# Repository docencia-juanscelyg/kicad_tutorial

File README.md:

# Tutorial KiCad

En este breve tutorial se guiará al estudiante en el uso básico del software KiCad. Este software permite diseñar circuitos impresos, es ampliamente usado en la comunidad open source y permite realizar diseños de ingeniería de producto.

<details>
<summary><b>Contenido</b></summary>

- [Instalación](#instalación)
  - [Repositorios de Ubuntu (recomendado)](#repositorios-de-ubuntu-recomendado)
  - [PPA oficial de KiCad](#ppa-oficial-de-kicad)
  - [Flatpak](#flatpak)
  - [Otras plataformas](#otras-plataformas)
  - [Comprobar la instalación](#comprobar-la-instalación)
- [Entorno inicial de trabajo](#entorno-inicial-de-trabajo)
- [Entorno de edición de esquemas](#entorno-de-edición-de-esquemas)
  - [Edición del cajetín](#edición-del-cajetín)
  - [Añadir símbolos](#añadir-símbolos)
  - [Unión entre símbolos](#unión-entre-símbolos)
  - [Añadir símbolos de alimentación](#añadir-símbolos-de-alimentación)
  - [Modificar la huella de un símbolo](#modificar-la-huella-de-un-símbolo)
- [Entorno de edición de placas](#entorno-de-edición-de-placas)
  - [Creación del Edge Cuts](#creación-del-edge-cuts)
  - [Traer o actualizar los cambios desde el esquema](#traer-o-actualizar-los-cambios-desde-el-esquema)
  - [Definir la zona de relleno](#definir-la-zona-de-relleno)
  - [Ubicación de huellas](#ubicación-de-huellas)
  - [Añadir agujeros de montaje](#añadir-agujeros-de-montaje)
  - [Ejecutar el DRC](#ejecutar-el-drc)
  - [Enrutado](#enrutado)
  - [Visualización 3D](#visualización-3d)
  - [Envío a fabricación](#envío-a-fabricación)

</details>

## Instalación

Este tutorial y el proyecto de ejemplo ([ejercicio_1](ejercicio_1/)) se han realizado con **KiCad 7.0** sobre **Ubuntu 24.04**, por lo que se recomienda usar esa misma versión.

> **Importante:** KiCad puede abrir proyectos de versiones anteriores, pero **no** de versiones posteriores. Un proyecto guardado con KiCad 8 o superior ya no se podrá abrir con KiCad 7. Si se trabaja en equipo, todos los miembros deben usar la misma versión.

### Repositorios de Ubuntu (recomendado)

Es la forma más sencilla y la que instala KiCad 7.0 en Ubuntu 24.04. Abrimos una terminal y escribimos:

```bash
sudo apt update
sudo apt install kicad
```

Este comando instala el programa junto con las bibliotecas de símbolos y huellas. La interfaz en español ya viene incluida, por lo que no hace falta instalar ningún paquete de idioma adicional. Opcionalmente se pueden instalar:

- **Modelos 3D de los componentes** (necesarios para la sección de [Visualización 3D](#visualización-3d) y para exportar a `STEP`). Ocupan unos 5,7 GB:

    ```bash
    sudo apt install kicad-packages3d
    ```

- **Ayuda en español** (manuales accesibles desde el menú `Ayuda`):

    ```bash
    sudo apt install kicad-doc-es
    ```

### PPA oficial de KiCad

Si se necesita una versión más reciente, el equipo de KiCad mantiene un repositorio PPA para Ubuntu. Hay un PPA por cada versión principal; en el siguiente ejemplo se usa la 9.0, aunque se puede consultar cuál es la última en la [página de descargas para Ubuntu](https://www.kicad.org/download/ubuntu/):

```bash
sudo add-apt-repository ppa:kicad/kicad-9.0-releases
sudo apt update
sudo apt install kicad
```

> **Nota:** al añadir el PPA, la versión de KiCad 7 instalada desde los repositorios de Ubuntu se sustituirá por la del PPA. Recuerda que los proyectos guardados con esta versión no se podrán abrir en KiCad 7.

### Flatpak

Flatpak permite instalar la última versión de KiCad en cualquier distribución de Linux, de forma aislada del resto del sistema. Si Flatpak no está instalado en Ubuntu, primero hay que instalarlo y añadir el repositorio Flathub (después conviene cerrar sesión y volver a entrar):

```bash
sudo apt install flatpak
flatpak remote-add --if-not-exists flathub https://dl.flathub.org/repo/flathub.flatpakrepo
```

A continuación instalamos KiCad y lo ejecutamos:

```bash
flatpak install flathub org.kicad.KiCad
flatpak run org.kicad.KiCad
```

Los modelos 3D se instalan aparte con `flatpak install flathub org.kicad.KiCad.Library.Packages3D`. Al ejecutarse en un entorno aislado, puede que KiCad no tenga acceso a todas las carpetas del sistema; se recomienda guardar los proyectos dentro de la carpeta personal.

### Otras plataformas

Para Windows, macOS u otras distribuciones de Linux, se puede consultar la [página de descargas de KiCad](https://www.kicad.org/download/).

### Comprobar la instalación

Una vez instalado, KiCad aparecerá en el menú de aplicaciones; también se puede lanzar desde una terminal con el comando `kicad` (o `flatpak run org.kicad.KiCad` si se instaló con Flatpak). La versión instalada se puede consultar en el menú `Ayuda` → `Acerca de KiCad`.

## Entorno inicial de trabajo

Existen dos entornos de trabajo principales: el editor de esquemas y el editor de placas. KiCad incluye otros entornos con los que no trabajaremos en este tutorial. Al abrir el programa aparecerá una ventana principal desde la que podremos gestionar los proyectos que creemos o queramos editar.

Desde esta ventana podremos editar cualquiera de los esquemas del proyecto creado o cargado.

## Entorno de edición de esquemas

En este entorno podremos editar los esquemas de los circuitos que hemos planteado. Aquí se eligen los componentes con los que vamos a trabajar, tanto sus huellas como sus conexiones. Desde este entorno también podremos acceder a otros editores de elementos. El entorno de edición de esquemas se muestra en la siguiente imagen.

A continuación exploraremos varios componentes de este entorno.

### Edición del cajetín

Para editar el cajetín basta con hacer doble clic sobre él y rellenar la información según corresponda. En él se puede incluir información útil para el equipo de trabajo o de cara a la fabricación. La ventana donde se edita dicha información se muestra a continuación.

### Añadir símbolos

Para añadir símbolos al diseño actual basta con ir a la barra de la derecha de la interfaz y pulsar el icono con forma de amplificador operacional; también se puede usar el atajo de teclado `A`. Se abrirá la biblioteca de símbolos, donde podremos seleccionar los elementos que queremos añadir a nuestro esquema.

Podemos usar la caja de búsqueda situada en la parte superior de la ventana para buscar la referencia del dispositivo que deseamos añadir. Del mismo modo, al elegir el símbolo del dispositivo, tendremos que elegir una huella asociada a él.

En este punto debemos elegir correctamente la huella de nuestro símbolo, teniendo en cuenta si se trata de un dispositivo SMD, THT o de otro tipo.

### Unión entre símbolos

Para unir símbolos debemos situar el ratón sobre los terminales de los dispositivos que queremos conectar. El cursor cambiará a una línea con un símbolo `+`, lo que indica que podemos unir dichos terminales.

### Añadir símbolos de alimentación

Para añadir un símbolo de alimentación basta con ir a la barra de la derecha del editor de esquemas y pulsar el botón con forma de tierra (`GND`); otra forma es mediante la tecla `P`.

Se debe seleccionar cada uno de los símbolos de alimentación que requiera el diseño, añadiendo tantas fuentes de alimentación como sean necesarias. Además, la alimentación necesitará un componente físico (por ejemplo, un conector) para poder ubicarse en el circuito impreso.

Al añadir los símbolos de alimentación conviene asociarlos a su respectiva huella. Veamos el caso en el que hemos elegido como conector de alimentación el dispositivo `J1 Screw_Terminal_01x02`. Este dispositivo no tiene una huella asociada, por lo que tendremos que añadirla. Para ello haremos doble clic sobre el dispositivo y abriremos su configuración.

Haremos clic en el campo de la huella, que aún está vacío, e iremos a la biblioteca de huellas, donde buscaremos una que se ajuste a las necesidades del conector que queremos utilizar. En este caso hemos elegido la huella `Connector_JST:JST_EH_S2B-EH_1x02_P2.50mm_Horizontal`, un conector JST de 2 pines con una separación de 2,5 mm en horizontal. Sin embargo, en la imagen podemos observar uno en vertical.

### Modificar la huella de un símbolo

Antes de pasar a la edición del circuito impreso, nos hemos dado cuenta de que el interruptor `SW Wuerth` tiene una huella que no nos conviene para nuestro diseño. Siguiendo el procedimiento descrito anteriormente para los conectores de alimentación, modificaremos la huella de este símbolo: hacemos doble clic sobre él, editamos el campo de la huella y elegimos una nueva de la biblioteca.

Con esto el esquemático quedaría terminado y podríamos pasar a la edición del circuito impreso.

## Entorno de edición de placas

En este entorno se realiza la edición de las placas. Se puede partir de un diseño esquemático o trabajar con huellas desde cero; evidentemente, lo recomendable es editar la placa a partir de un esquemático previo. Para abrir el editor basta con hacerlo desde la ventana principal del software o, desde el editor de esquemas, pulsar el botón de circuito impreso.

En este entorno se puede editar el cajetín de la misma forma que en el editor de esquemas. A continuación describiremos algunos elementos propios de este entorno:

- **Capas:** podemos gestionar las diferentes capas del diseño desde el panel de la derecha. Para seleccionar una capa concreta usaremos el selector que aparece en la barra de herramientas superior.
- **Reglas de diseño:** aunque el software ofrece muchas ayudas para el trazado de pistas, en la parte superior existe un botón para verificar las reglas de diseño del circuito (DRC).
- **Actualizar desde el esquema:** para no tener que traer las huellas una por una, existe un botón que las importa desde el esquemático asociado al proyecto.

En este entorno de trabajo podremos visualizar:

- **Soldermask:** máscara de soldadura.
- **Silkscreen:** capa de serigrafía.
- **Layout:** el diseño de la placa.
- **Pad:** zona de contacto de un pin.
- **Net:** conexión eléctrica entre dos o más componentes.
- **Rat (ratsnest):** conexión de una net que aún no se ha trazado en el layout.
- **Traza (pista):** conexión de una net que ya se ha trazado en el layout.
- **Vía:** conexión entre capas.

Cada uno de estos elementos dispone de un botón o una herramienta para su diseño o gestión.

> **Nota:** todos los valores por defecto del editor de placas se pueden configurar desde un icono situado a la izquierda de la barra de herramientas, debajo del menú `Archivo`.

### Creación del Edge Cuts

Lo primero que debemos crear es el contorno de nuestra placa. Para ello dibujaremos la geometría deseada con las herramientas de dibujo. No hay que olvidar tener seleccionada la capa `Edge.Cuts` para que dicha geometría se defina como el contorno de la placa.

### Traer o actualizar los cambios desde el esquema

Una vez definido el contorno de la placa, traeremos las huellas desde el esquema mediante el botón **Actualizar placa desde esquema** de la parte superior.

Al traer los cambios desde el esquema se realiza un análisis de los posibles errores. En nuestro caso, uno de los pines del interruptor no está asociado a la huella, un error menor que no altera el funcionamiento del circuito. A continuación podremos ver las huellas importadas.

### Definir la zona de relleno

Una buena práctica en el diseño de circuitos impresos es usar zonas de relleno para evitar desbastar material innecesariamente. En la barra lateral derecha está la herramienta de creación de zonas de relleno; seleccionaremos una net (normalmente `GND`) para que todas las rats de esa net se conecten a la zona. Es importante tener seleccionada la capa en la que se va a crear la zona; en nuestro caso, la capa inferior (`B.Cu`, *Bottom Layer*).

### Ubicación de huellas

En este apartado lo importante es colocar las huellas de manera que no se solapen entre sí. Al traerlas desde el esquemático aparecen agrupadas para reducir el espacio; en este ejercicio las vamos a separar. Ubicamos los componentes como consideremos oportuno.

### Añadir agujeros de montaje

Para poder fijar la placa a una base rígida, añadiremos agujeros de montaje. Se encuentran en el catálogo de huellas del panel derecho. En nuestro caso seleccionamos unos para tornillos de 3 mm.

Los ubicaremos según la disponibilidad de nuestro diseño mecánico. Podemos usar herramientas como la regla o la rejilla de fondo. Hay que recordar que dicha rejilla está en milésimas de pulgada (*mils*), que es la unidad en la que están diseñados la mayoría de los dispositivos; si la cambiamos a milímetros podemos tener problemas a la hora de colocar componentes. Para los agujeros de montaje podemos usar la rejilla en milímetros y para los dispositivos eléctricos la rejilla en pulgadas.

Conviene quitar la serigrafía de los agujeros de montaje para simplificar la capa de silkscreen.

### Ejecutar el DRC

Para verificar que hasta el momento todo va bien ejecutaremos el DRC (*Design Rules Check*) mediante el botón con forma de lista de verificación de la parte superior. En la ventana que se abre pulsaremos `Ejecutar DRC`, lo que validará las reglas de diseño sobre todo lo realizado hasta el momento.

Si todo va bien, veremos que no aparecen errores y que la zona de relleno se ha rellenado. Las rats son visibles, pero aún no hay trazas.

### Enrutado

En este tutorial se muestra un enrutado manual; KiCad también dispone de herramientas de enrutado automático, pero no forman parte de este tutorial. Para enrutar basta con pulsar el botón **Enrutar pistas** del panel derecho o la tecla `X`.

Al terminar el enrutado, la zona de relleno no se visualizará correctamente. Primero nos aseguramos de haber completado todo el enrutado.

Para que se actualicen las zonas de relleno tendremos que ejecutar de nuevo el DRC, como se ha explicado en la sección anterior (también se puede usar la tecla `B` para rellenar todas las zonas).

### Visualización 3D

Es posible ver el circuito terminado en 3D desde el menú `Ver` → `Visor 3D`, o con la combinación de teclas `Alt+3`.

El modelo se puede exportar a formato `STEP` desde el menú `Archivo` → `Exportar`, seleccionando dicho formato. Este archivo se puede importar en FreeCAD para editarlo o usarlo en otro diseño.

### Envío a fabricación

Para generar los archivos de fabricación, desde el menú `Archivo` seleccionamos `Salidas de fabricación` → `Gerbers`. Los archivos generados son los que enviaremos al fabricante.

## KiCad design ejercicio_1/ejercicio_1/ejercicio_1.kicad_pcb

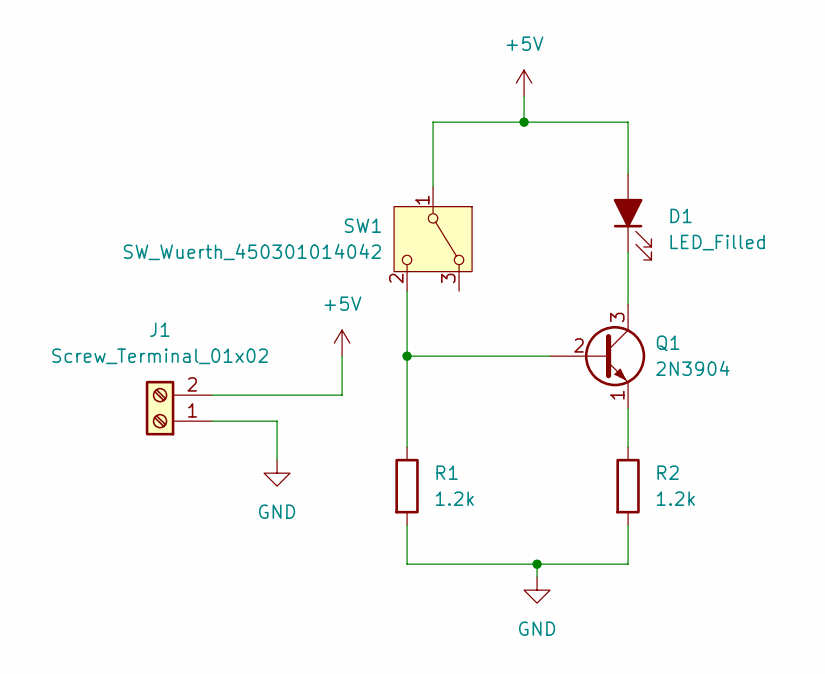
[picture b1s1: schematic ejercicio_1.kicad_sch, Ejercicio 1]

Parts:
D1: LED_Filled; LED_D3.0mm
J1: Screw_Terminal_01x02; JST_EH_S2B-EH_1x02_P2.50mm_Horizontal
Q1: 2N3904; TO-92_Inline
R1, R2: 1.2k; R_Axial_DIN0204_L3.6mm_D1.6mm_P5.08mm_Horizontal
SW1: SW_Wuerth_450301014042; SW_PUSH_6mm

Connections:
+5V: D1.2 (A), J1.2, SW1.1 (B)
GND: J1.1, R1.2, R2.2
unnamed: D1.1 (K), Q1.3 (C)
unnamed: Q1.2 (B), R1.1, SW1.2 (C)
unnamed: Q1.1 (E), R2.1

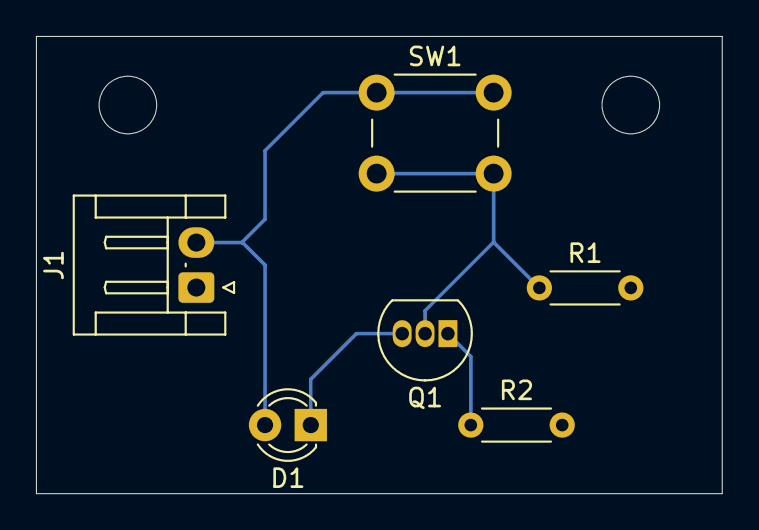
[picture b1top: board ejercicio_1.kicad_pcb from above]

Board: 2 copper layers, 38.1 x 25.4 mm, 6 parts (0 on the bottom side), 5 nets.
